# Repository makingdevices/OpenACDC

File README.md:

<!-- Improved compatibility of back to top link: See: https://github.com/othneildrew/Best-README-Template/pull/73 -->

<!--
*** Thanks for checking out the Best-README-Template. If you have a suggestion
*** that would make this better, please fork the repo and create a pull request
*** or simply open an issue with the tag "enhancement".
*** Don't forget to give the project a star!
*** Thanks again! Now go create something AMAZING! :D
-->

<!-- PROJECT SHIELDS -->
<!--
*** I'm using markdown "reference style" links for readability.
*** Reference links are enclosed in brackets [ ] instead of parentheses ( ).
*** See the bottom of this document for the declaration of the reference variables
*** for contributors-url, forks-url, etc. This is an optional, concise syntax you may use.
*** https://www.markdownguide.org/basic-syntax/#reference-style-links
-->
[![Instagram][ig-shield]][ig-url]
[![PCBWAY][sponsor-shield]][sponsor-url]
[![Stargazers][stars-shield]][stars-url]
[![Issues][issues-shield]][issues-url]
[![LinkedIn][linkedin-shield]][linkedin-url]

<!-- PROJECT LOGO -->
<br />
<div align="center">

<h3 align="center">Making Devices</h3>

  <p align="center">
    Open Source projects where we struggle with engineering, electronics, coding and who knows what else... In this case, OpenACDC is a simple SMPS power supply to test their capabilities, so hopefully you may find it interesting ;)
  </p>
</div>

<!-- TABLE OF CONTENTS -->
<details>
  <summary>Table of Contents</summary>
  <ol>
    <li>
      <a href="#about-the-project">About The Project</a>
      <ul>
        <li><a href="#built-with">Built With</a></li>
      </ul>
    </li>
    <li>
      <a href="#Build-one">Build one</a>
      <ul>
      </ul>
    </li>
    <li><a href="#usage">Usage</a></li>
    <li><a href="#roadmap">Roadmap</a></li>
    <li><a href="#license">License</a></li>
    <li><a href="#contact">Contact</a></li>
    <li><a href="#Sponsor">Sponsor</a></li>
  </ol>
</details>

<!-- ABOUT THE PROJECT -->
## About The Project

[![Bytes Counter Shot][product-screenshot]](https://github.com/makingdevices/OpenACDC)

The Open SMPS is a small Switched Mode Power Supply for testing purposes, nothing special. It has 5W output rating, and it converts main power to 5V - 1A

This device is under development, so I do encourage you to not assembly, order any PCB or use any software from this repository until the project is finished.

<p align="right">(<a href="#readme-top">back to top</a>)</p>

### Built With

[![Kicad][kicad-shield]][kicad-url]
[![SPONSOR][sponsor-icon]][sponsor-url]

<p align="right">(<a href="#readme-top">back to top</a>)</p>

<!-- GETTING STARTED -->

## Build one
NOT RECOMMENDED AS THE DEVICE IS UNDER DEVELOPMENT

<p align="right">(<a href="#readme-top">back to top</a>)</p>

<!-- USAGE EXAMPLES -->
## Usage

Instructions of use:

- As soon as you connect the main power, the output voltage will be activated

<p align="right">(<a href="#readme-top">back to top</a>)</p>

<!-- ROADMAP -->
## Roadmap

- [ ] Test/Validate the project.
- [ ] Re-assembly another board.

See the [open issues](https://github.com/makingdevices/OpenACDC/issues) for a full list of proposed features (and known issues).

State: Project <b>UNFINISHED</b> - 07/01/2023

Priority: <b>Low</b>

<p align="right">(<a href="#readme-top">back to top</a>)</p>

<!-- LICENSE -->
## License

Distributed under three licenses:
- [Hardware](/License/HW_cern_ohl_s_v2.pdf)
- [Software](/License/SW_GPLv3.0.txt)
- [Documentation](/License/Documentation_CC-BY-SA-4.0.txt)

[![GPL v3 License][license-shield]][license-url] 
<p align="right">(<a href="#readme-top">back to top</a>)</p>

<!-- CONTACT -->
## Contact

Making Devices - [@MakingDevices](https://www.instagram.com/makingdevices/)

Project Link: [https://github.com/makingdevices/OpenReflowPlate](https://github.com/makingdevices/OpenACDC/)

Other Links: [LinkTree](https://makingdevices.com/links/)

<p align="right">(<a href="#readme-top">back to top</a>)</p>

<!-- MARKDOWN LINKS & IMAGES -->
<!-- https://www.markdownguide.org/basic-syntax/#reference-style-links -->
[contributors-shield]: https://img.shields.io/github/contributors/makingdevices/OpenACDC.svg?style=for-the-badge
[contributors-url]: https://github.com/makingdevices/OpenACDC/graphs/contributors
[forks-shield]: https://img.shields.io/github/forks/makingdevices/OpenACDC.svg?style=for-the-badge
[forks-url]: https://github.com/makingdevices/OpenACDC/network/members
[stars-shield]: https://img.shields.io/github/stars/makingdevices/OpenACDC.svg?style=for-the-badge
[stars-url]: https://github.com/makingdevices/OpenACDC/stargazers
[issues-shield]: https://img.shields.io/github/issues/makingdevices/OpenACDC.svg?style=for-the-badge
[issues-url]: https://github.com/makingdevices/OpenACDC/issues
[license-shield]: /images/license.png
[license-url]: https://github.com/makingdevices/OpenACDC/tree/main/License
[linkedin-shield]: https://img.shields.io/badge/-LinkedIn-black.svg?style=for-the-badge&logo=linkedin&colorB=555
[linkedin-url]: https://www.linkedin.com/company/making-devices/
[sponsor-shield]: https://img.shields.io/badge/SPONSOR-PCBWAY-black.svg?style=for-the-badge&colorB=1200
[sponsor-url]: https://www.pcbway.com/?from=makingdevices
[sponsor-screenshot]: /images/PCB_sponsor.png
[product-screenshot]: images/screenshot.jpg
[PIC]: https://img.shields.io/badge/PIC18LF45K50-000000?style=for-the-badge
[PIC-url]: http://ww1.microchip.com/downloads/en/devicedoc/40001350f.pdf
[kicad-shield]: https://img.shields.io/badge/kicad-0b03fc?style=for-the-badge&logo=kicad&logoColor=white
[kicad-url]: https://www.kicad.org/
[YT-screenshot]: images/YT_assembly.PNG
[sponsor-icon]:  https://img.shields.io/badge/-PCBWAY-black.svg?style=for-the-badge&colorB=1200
[ig-shield]: https://img.shields.io/badge/instagram-a83297?style=for-the-badge&logo=instagram&logoColor=white
[ig-url]: https://www.instagram.com/makingdevices/
[MPLAB-C]: https://img.shields.io/badge/MPLAB%20C18-DD0031?style=for-the-badge&logo=C&logoColor=white
[MPLAB-C-url]: https://www.microchip.com/en-us/development-tool/SW006011
[Svelte.dev]: https://img.shields.io/badge/Svelte-4A4A55?style=for-the-badge&logo=svelte&logoColor=FF3E00
[Svelte-url]: https://svelte.dev/
[Laravel.com]: https://img.shields.io/badge/Laravel-FF2D20?style=for-the-badge&logo=laravel&logoColor=white
[Laravel-url]: https://laravel.com
[Bootstrap.com]: https://img.shields.io/badge/Bootstrap-563D7C?style=for-the-badge&logo=bootstrap&logoColor=white
[Bootstrap-url]: https://getbootstrap.com
[JQuery.com]: https://img.shields.io/badge/jQuery-0769AD?style=for-the-badge&logo=jquery&logoColor=white
[JQuery-url]: https://jquery.com

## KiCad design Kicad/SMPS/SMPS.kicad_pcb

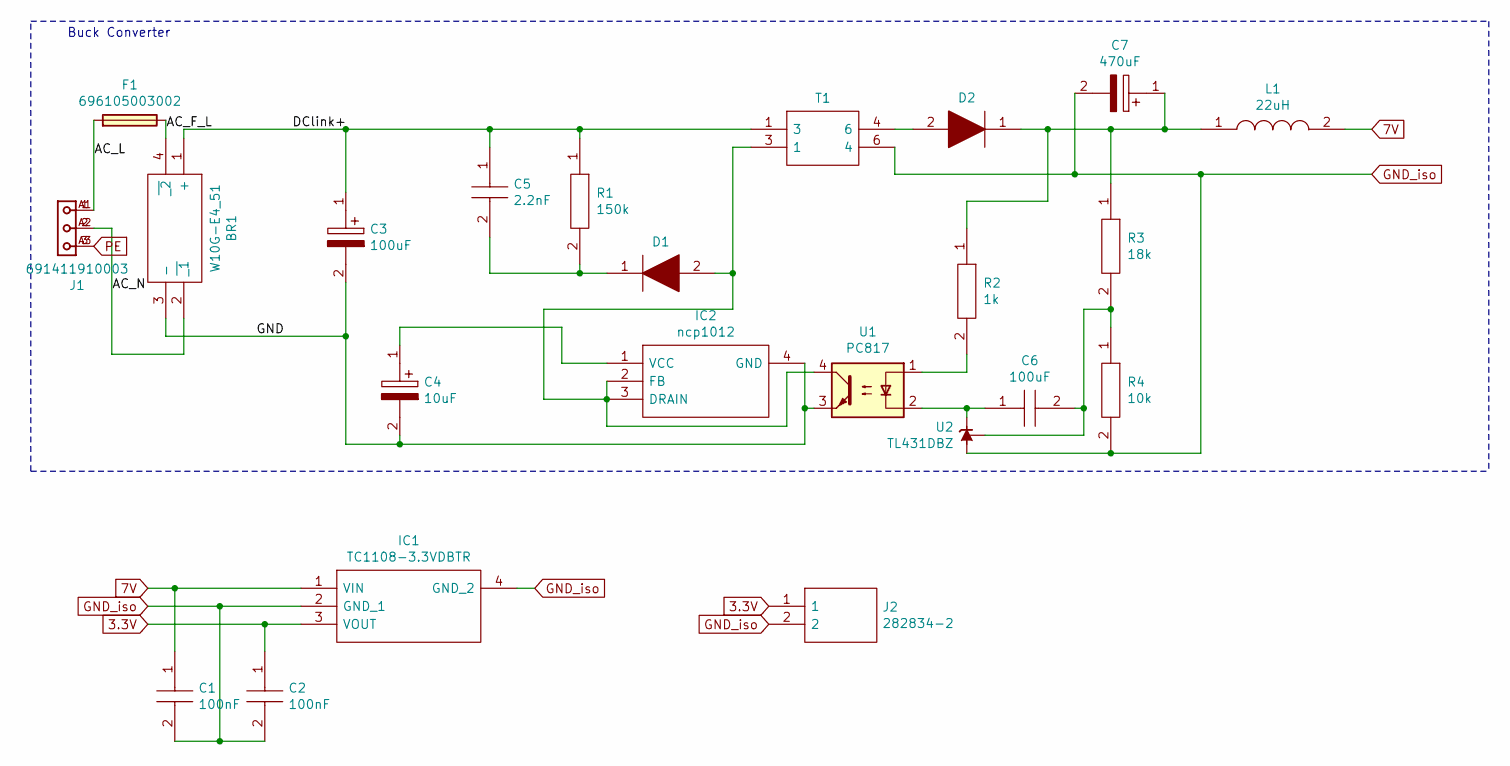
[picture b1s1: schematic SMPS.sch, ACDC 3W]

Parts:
BR1: W10G-E4_51; WOG_8.84X5.6__1; Mouser Part Number 625-W10G-E4
C1, C2: 100nF; CAPC2012X140N; Manufacturer_Part_Number C0805C475M8RACTU
C3: 100uF; CAPPRD750W80D1825H2700; Manufacturer_Part_Number 400BXW100MEFR18X25
C4: 10uF; CAPAE430X610N; Mouser Part Number 598-AVE106M16B12T-F
C5: 2.2nF; B32620__10_x_4_; Mouser Part Number 871-B32620A6222K189
C6: 100uF; CAPC2012X140N; Manufacturer_Part_Number C0805C475M8RACTU
C7: 470uF; CAPAE830X1250N; Mouser Part Number 80-A768KS477M1CLAE17
D1: AU1PJ-M3_84A; DO-220AA; Mouser Part Number 625-AU1PJ-M3/84A
D2: VS-MBRS360-M3_9AT; DIOM7959X262N; Mouser Part Number 78-VS-MBRS360-M39AT
F1: 696105003002; FUSE_696105003002
IC1: TC1108-3.3VDBTR; SOT230P700X180-4N; Manufacturer_Part_Number TC1108-3.3VDBTR
IC2: ncp1012; SOT230P700X175-4N; Mouser Part Number 863-NCP1012ST130T3G
J1: 691411910003; PART-NUMBER 691411910003
J2: 282834-2; 282834-2_1; Mouser Part Number 571-282834-2
L1: 22uH; MSS1048223MLB; Mouser Part Number 994-MSS1048-223MLB
R1: 150k; RESC2012X75N; Manufacturer_Part_Number ERJP6WF1303V
R2: 1k; RESC2012X75N; Manufacturer_Part_Number ERJP6WF1303V
R3: 18k; RESC2012X75N; Manufacturer_Part_Number ERJP6WF1303V
R4: 10k; RESC2012X75N; Manufacturer_Part_Number ERJP6WF1303V
T1: 7491181012; WE_E13/7/4_THT_VERTIKAL_6PIN112; Mouser Part Number 710-7491181012
U1: PC817; DIP-4_W7.62mm
U2: TL431DBZ; SOT-23

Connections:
3.3V: C2.1, IC1.3 (VOUT), J2.1
7V: C1.1, IC1.1 (VIN), L1.2
/AC_F_L: BR1.4 (~_2), F1.2
/AC_L: F1.1, J1.1, J1.A1
/AC_N: BR1.2 (~_1), J1.2, J1.A2
/DClink+: BR1.1 (+), C3.1, C5.1, R1.1, T1.1 (3)
/GND: BR1.3 (-), C3.2, C4.2, IC2.4 (GND), U1.3
GND_iso: C1.2, C2.2, C7.2, IC1.2 (GND_1), IC1.4 (GND_2), J2.2, R4.2, T1.6 (4), U2.3 (A)
unnamed: C4.1, IC2.1 (VCC)
unnamed: C5.2, D1.1, R1.2
unnamed: C6.1, U1.2, U2.1 (K)
unnamed: C6.2, R3.2, R4.1, U2.2 (REF)
unnamed: C7.1, D2.1, L1.1, R2.1, R3.1
unnamed: D1.2, IC2.2 (FB), IC2.3 (DRAIN), T1.3 (1), U1.4
unnamed: D2.2, T1.4 (6)
unnamed: R2.2, U1.1
PE: J1.3, J1.A3

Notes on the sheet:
Buck Converter

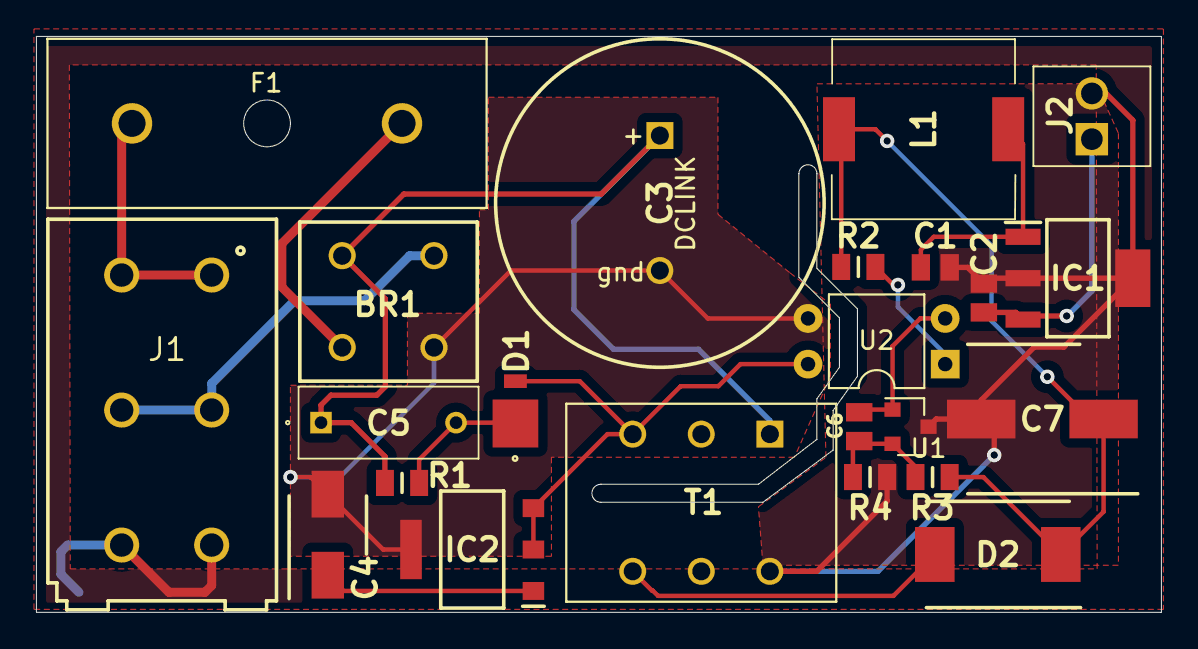
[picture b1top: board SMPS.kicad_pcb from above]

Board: 2 copper layers, 62.5 x 32.0 mm, 23 parts (0 on the bottom side), 17 nets.

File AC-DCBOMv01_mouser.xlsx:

| Part | Info | Qty. | Unit Price | Ext. Price | Mouser Ref | Link
x | AC connector | Fixed Terminals AC | 1 | 1.41 | 1.41 | 710-691411910003
 | Fuse | Fuse Holder | 1 | 0.57799999999999996 | 0.57799999999999996 | 710-696105003002
x | Fuse cover | Fuse holder cover | 1 | 0.21 | 0.21 | 710-696122003001
x | 2W10G-E4/51 | Bridge Rectifier 2A | 1 | 0.60399999999999998 | 0.60399999999999998 | 625-2W10G-E4
x | 82uF RubyCon | 82uF capacitor | 1 | 2.64 | 2.64 | 232-400BXW82MEFR18X2
x | 10uF Cap | 10uF Cap | 1 | 0.39400000000000002 | 0.39400000000000002 | 598-AVE106M16B12T-F
x | 22nF Cap | 22nF | 1 | 0.54500000000000004 | 0.54500000000000004 | 871-B32620A6222K189
x | 18 K resistor | 18K 0805 | 1 | 0.21 | 0.21 | 279-CRGP0805F18K
x | 150K Resistor | 150k 0805 | 1 | 0.22800000000000001 | 0.22800000000000001 | 279-CRGCQ0805F150K
x | Rectifier Ultrafast | 600V 1A | 1 | 0.42 | 0.42 | 625-AU1PJ-M3/84A
x | NCP1012 | NCP1012 smd | 1 | 1.03 | 1.03 | 863-NCP1012ST100T3G
x | Flyback We-Unit | WE-UNIT AC flyback | 1 | 6.35 | 6.35 | 710-7491181012
x | Optocoupler | Optocoupler DIP | 1 | 0.34100000000000003 | 0.34100000000000003 | 852-PC817X1NSZ1B
x | 3A 60v Diode | Vishay Rectifier diode | 1 | 0.46400000000000002 | 0.46400000000000002 | 625-SS36-E3
x | 470uF | KEMET | 1 | 0.84 | 0.84 | 80-A768KS477M1CLAE17
x | TL431 | TL431 TI smd | 1 | 1.01 | 1.01 | 595-TL431LIBEDBZRQ1
x | 22uH Coil | Coil smd | 1 | 1.62 | 1.62 | 994-MSS1048-223MLC
 | LDO 300mA 3.3V | 3.3V LDO | 1 | 0.58599999999999997 | 0.58599999999999997 | 579-TC1108-3.3VDBTR
 | Output Connector | 2pin connector | 1 | 1.1200000000000001 | 1.1200000000000001 | 571-282834-2
x | 100nF Cap |  | 3 | 0.14000000000000001 | 0.42000000000000004 | 581-08055C104K
 |  |  |  |  | Total: | 21.020000000000003

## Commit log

2023-01-07 Update Files
2023-01-07 New device image
2023-01-07 no message
